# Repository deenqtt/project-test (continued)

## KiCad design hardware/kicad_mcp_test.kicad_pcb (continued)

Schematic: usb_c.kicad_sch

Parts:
D1: USBLC6-2SC6; SOT-23-6; MPN USBLC6-2SC6
J1: USB4105-GF-A; USB_C_Receptacle_GCT_USB4105-xx-A_16P_TopMnt_Horizontal; MPN USB4105-GF-A
R1, R41: 5.1k 1%; R_0603_1608Metric
R40: 1k 1%; R_0603_1608Metric
R42, R46: 22R 1%; R_0603_1608Metric
R45: 39k 1%; R_0603_1608Metric

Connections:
3V3_LOGIC: R40.2; also elsewhere on the board
/USB_C/USB_CC1: J1.A5 (CC1), R41.1
/USB_C/USB_CC2: J1.B5 (CC2), R1.1
/USB_C/USB_D_N_CONN: D1.1 (I/O1), J1.A7 (D-), J1.B7 (D-)
/USB_C/USB_D_N_ESD: D1.6 (I/O1), R46.1
/USB_C/USB_D_P_CONN: D1.3 (I/O2), J1.A6 (D+), J1.B6 (D+)
/USB_C/USB_D_P_ESD: D1.4 (I/O2), R42.1
/USB_C/USB_VBUS: D1.5 (VBUS), J1.A4 (VBUS), J1.A9 (VBUS), J1.B4 (VBUS), J1.B9 (VBUS), R45.1
LOGIC_GND: D1.2 (GND), J1.A1 (GND), J1.A12 (GND), J1.B1 (GND), J1.B12 (GND), J1.S1 (SHIELD), R1.2, R41.2; also elsewhere on the board
USB_D_N: R46.2; also elsewhere on the board
USB_D_P: R42.2; also elsewhere on the board
USB_VBUS_DET_GATE: R45.2; also elsewhere on the board
USB_VBUS_DET_N: R40.1; also elsewhere on the board

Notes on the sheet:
J10 = GCT USB4105-GF-A; CC1/CC2 each use 5.1k Rd to LOGIC_GND
LAYOUT LATER: 90R differential ±10%; short, matched, minimal vias/stubs
22R SERIES PARTS NEAR ESP32
Connector shield directly to LOGIC_GND; no fictitious chassis domain
ESD DEVICE NEAR CONNECTOR
Continuous LOGIC_GND reference; no isolation gap under pair
USB_VBUS IS SENSE/ESD REFERENCE ONLY — NEVER CONNECT TO BOARD POWER RAILS
USB-C NATIVE USB SERVICE — SELF-POWERED BOARD

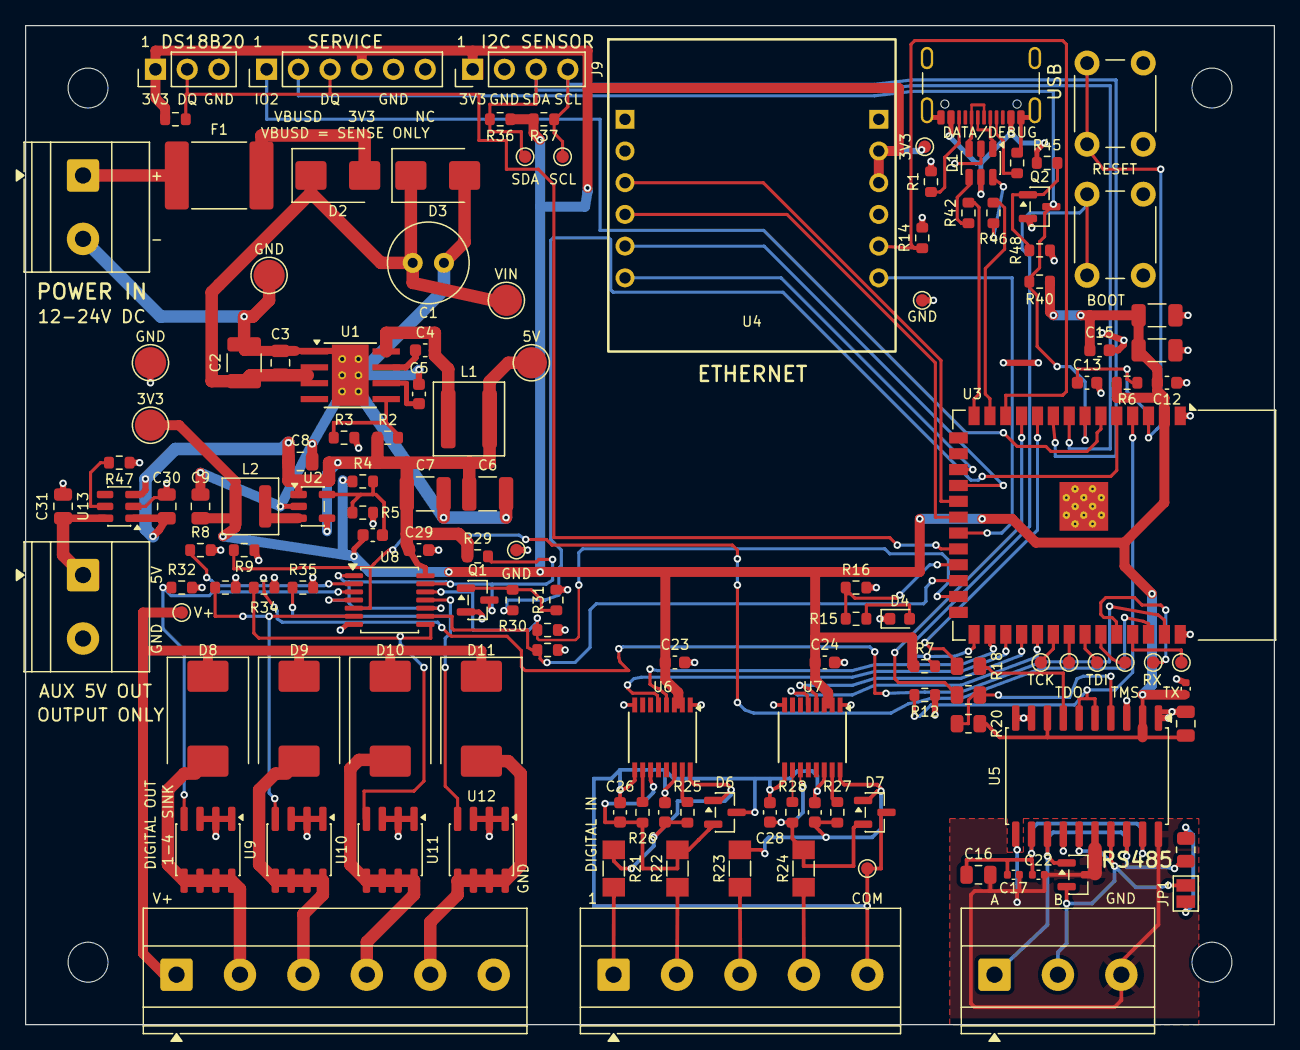
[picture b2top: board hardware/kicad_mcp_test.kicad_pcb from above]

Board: 2 copper layers, 100.0 x 80.0 mm, 136 parts (0 on the bottom side), 88 nets.

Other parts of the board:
H1, H2, H3, H4: MountingHole_3.2mm_M3
Q2: 2N7002-7-F; SOT-23
R48: 470k; R_0603_1608Metric

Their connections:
LOGIC_GND: Q2.2, R48.2; also elsewhere on the board
USB_VBUS_DET_GATE: Q2.1, R48.1; also elsewhere on the board
USB_VBUS_DET_N: Q2.3; also elsewhere on the board

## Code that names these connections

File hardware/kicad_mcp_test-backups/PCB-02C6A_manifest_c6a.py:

# PCB-02C6A candidate manifest (geometry-as-code). All vias 0.6/0.3. Widths per net.
M={}
M['USB_VBUS']=('/USB_C/USB_VBUS',
  [('F.Cu',[(74.1,7.355),(74.1,8.7),(73.95,8.85)],0.4),
   ('B.Cu',[(73.95,8.85),(75.8,10.7),(76.1,11.0),(76.5,11.0)],0.4)],
  [(73.95,8.85)])
M['TP12']=('3V3_LOGIC',
  [('F.Cu',[(72.0,9.7),(71.75,9.95)],0.5),
   ('B.Cu',[(71.75,9.95),(71.66,10.04),(68.32,10.04)],0.5)],
  [(71.75,9.95)])
M['UART0_RX']=('/ESP32_CORE/UART0_RX',
  [('F.Cu',[(87.35,48.75),(87.35,47.75),(87.0,47.4),(86.35,47.4),(86.1,47.15),(86.1,46.2),(86.5,45.8),(88.8,45.8),(89.4,46.4),(90.9,46.4),(91.3,46.8)],0.25),
   ('B.Cu',[(91.3,46.8),(91.3,50.75)],0.25),
   ('F.Cu',[(91.3,50.75),(91.05,51.0),(90.3,51.0)],0.25)],
  [(91.3,46.8),(91.3,50.75)])
M['SPARE_GPIO2']=('SPARE_GPIO2',
  [('B.Cu',[(19.3,3.5),(19.3,7.5),(46.0,7.5),(46.0,16.4),(59.1,16.4),(75.3,32.6),(78.3,32.6)],0.25),
   ('F.Cu',[(78.3,32.6),(79.4,33.7),(81.7,33.7),(82.1,34.1),(85.0,34.1),(85.8,33.3),(85.8,32.6),(86.11,32.3),(86.11,31.25)],0.25)],
  [(78.3,32.6)])
M['SPARE_GPIO1']=('SPARE_GPIO1',
  [('F.Cu',[(39.0,46.825),(38.3,46.85)],0.25),
   ('B.Cu',[(38.3,46.85),(38.1,46.7),(36.2,46.7),(35.8,47.1),(35.8,47.9),(36.3,48.4),(37.2,48.4),(37.55,48.75),(42.35,48.75),(42.7,49.1),(43.6,49.1),(43.95,48.75),(43.95,46.83),(42.72,45.6),(42.72,43.33),(43.35,42.7),(43.35,42.25),(44.7,40.9),(64.2,40.9),(68.7,36.4),(76.3,36.4),(76.6,36.1)],0.25),
   ('F.Cu',[(76.6,36.1),(86.9,36.1),(87.38,35.62),(87.38,31.25)],0.25)],
  [(38.3,46.85),(76.6,36.1)])
ORDER=['USB_VBUS','TP12','UART0_RX','SPARE_GPIO2']
REWORK=['SPARE_GPIO1']

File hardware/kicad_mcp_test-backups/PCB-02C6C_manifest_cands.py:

# PCB-02C6B candidate manifests (geometry-as-code). Coordinates mm. Vias 0.6/0.3.
# remove items: ('trk', layer, (x1,y1),(x2,y2), net) or ('via', (x,y), net)
# add items:   (net, [(layer, [pts], width), ...], [vias])
DI4='/DIGITAL_INPUTS_ISOLATED/DI4_SENSE'; DI4IN='/DIGITAL_INPUTS_ISOLATED/DI4_IN'; FG='/DIGITAL_INPUTS_ISOLATED/DI_FIELD_GND'; DI3='/DIGITAL_INPUTS_ISOLATED/DI3_SENSE'
G1N='SPARE_GPIO1'; OE='/DIGITAL_OUTPUTS/DO_BUF_OE_N'; D4C='DO4_CTRL'; GND='LOGIC_GND'
C={}
# ---------------- DI4_SENSE candidate D1: GND row jog + GND via move + DI3_SENSE B row relocated + DI4_IN narrowed ----------------
C['D1']=dict(
 remove=[
  ('trk','F.Cu',(61.413,59.6),(61.413,61.9),DI4IN),                 # DI4_IN w0.3 -> replaced by w0.15 same geometry
  ('via',(63.2,61.2),FG), ('trk','B.Cu',(63.2,61.2),(63.2,60.3),FG), ('trk','B.Cu',(51.9,60.3),(63.2,60.3),FG),
  ('trk','B.Cu',(68.0,62.2),(68.5,61.7),DI3), ('trk','B.Cu',(60.5,62.2),(68.0,62.2),DI3), ('trk','B.Cu',(60.5,64.0),(60.5,62.2),DI3),
  ('trk','B.Cu',(59.2,65.3),(60.5,64.0),DI3), ('trk','B.Cu',(64.1,62.2),(64.1,65.0),DI3),
 ],
 add=[
  (DI4IN,[('F.Cu',[(61.413,59.6),(61.413,61.9)],0.15)],[]),
  (FG,[('F.Cu',[(63.35,61.2),(63.4,61.3)],0.3),('B.Cu',[(63.4,61.3),(63.4,60.1),(63.0,59.7),(61.8,59.7),(61.2,60.3),(51.9,60.3)],0.3)],[(63.4,61.3)]),
  (DI3,[('B.Cu',[(68.5,61.7),(68.5,64.3),(67.8,65.0),(59.5,65.0),(59.2,65.3)],0.3)],[]),
  (DI4,[("F.Cu",[(62.047,59.6),(62.047,60.445),(62.25,60.75),(62.25,60.95)],0.15),("B.Cu",[(62.25,60.95),(62.25,63.0),(61.45,63.8),(60.5,63.8)],0.3)],[(62.25,60.95),(60.5,63.8)]),
 ],
 target=DI4, touched_nets=[DI4IN,FG,DI3])
# ---------------- SPARE_GPIO1 candidate G1: DO4_CTRL feed re-laid south of R30, OE_N Q1.3 link re-laid north (loop removed) ----------------
LANE=[(42.7,45.6),(42.7,43.45),(42.9,43.25),(42.9,42.0),(42.05,41.15),(42.05,17.2),(42.25,17.0),(46.7,17.0),(46.85,17.15),(46.85,21.15),(47.05,21.35),(60.65,21.35),(75.4,36.1),(75.7,36.4),(76.3,36.4),(76.6,36.1)]
C['G1']=dict(
 remove=[
  ('trk','B.Cu',(33.259999,45.35),(40.5,45.35),D4C), ('trk','B.Cu',(40.5,45.35),(40.975,45.825),D4C), ('trk','B.Cu',(40.975,45.825),(40.975,47.45),D4C),
  ('via',(37.6,47.4),OE), ('trk','F.Cu',(37.138,46.0),(37.138,46.9),OE), ('trk','F.Cu',(37.138,46.9),(37.6,47.4),OE),
  ('trk','B.Cu',(37.6,47.9),(37.6,47.4),OE), ('trk','B.Cu',(37.9,48.2),(37.6,47.9),OE), ('trk','B.Cu',(41.9,48.2),(37.9,48.2),OE),
  ('trk','B.Cu',(42.2,47.9),(41.9,48.2),OE), ('trk','B.Cu',(42.2,44.4),(42.2,47.9),OE),
 ],
 add=[
  (D4C,[('B.Cu',[(33.26,45.35),(35.8,45.35),(35.8,48.4),(40.3,48.4),(40.975,47.725),(40.975,47.45)],0.25)],[]),
  (OE,[('F.Cu',[(37.138,46.0),(37.138,46.6),(37.35,46.85)],0.25),('B.Cu',[(37.35,46.85),(37.35,44.72)],0.25)],[(37.35,46.85)]),
  (G1N,[('F.Cu',[(39.0,46.825),(38.3,46.85)],0.25),('B.Cu',[(38.3,46.85),(38.55,46.6),(38.55,46.0),(41.6,46.0)]+LANE,0.25),('F.Cu',[(76.6,36.1),(86.9,36.1),(87.38,35.62),(87.38,31.25)],0.25)],[(38.3,46.85),(76.6,36.1)]),
 ],
 target=G1N, touched_nets=[D4C,OE])
